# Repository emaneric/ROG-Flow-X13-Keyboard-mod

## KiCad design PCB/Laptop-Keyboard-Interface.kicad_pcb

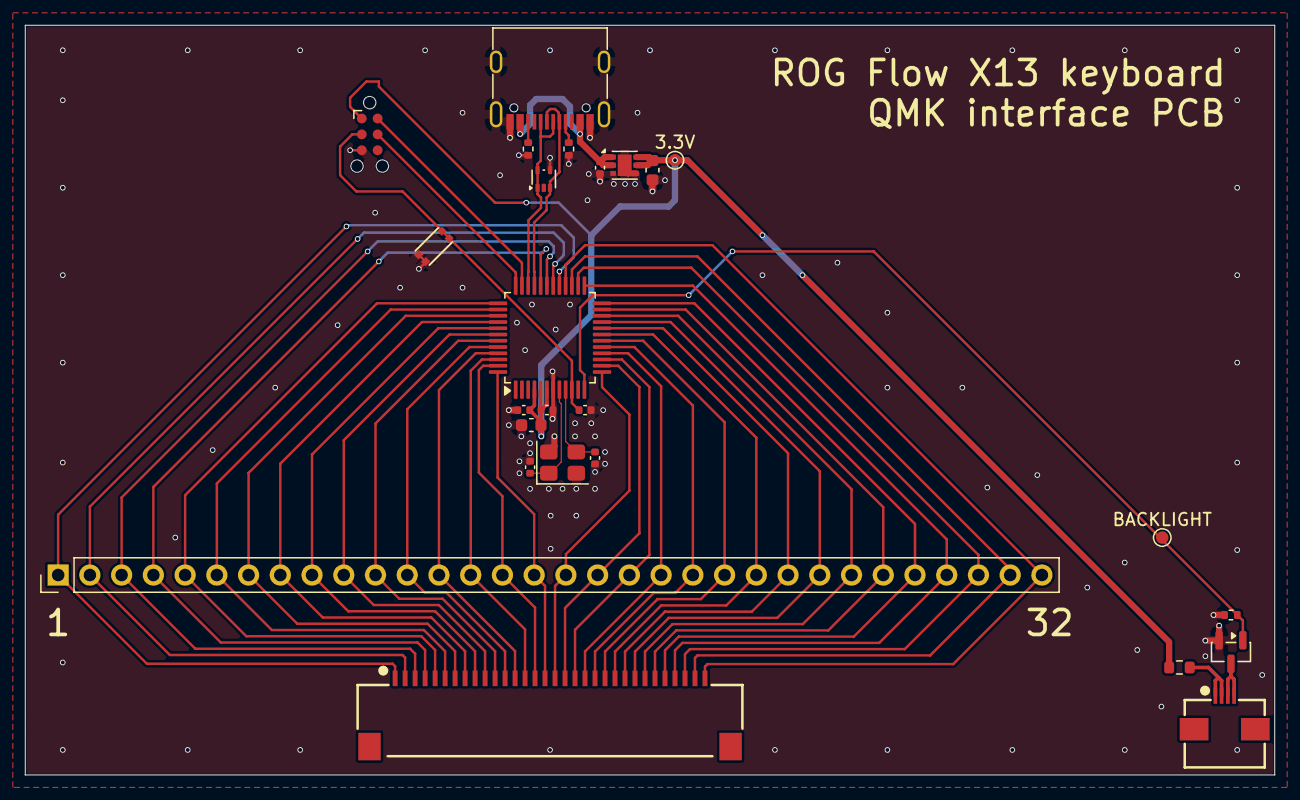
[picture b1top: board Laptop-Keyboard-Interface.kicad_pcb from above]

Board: 2 copper layers, 100.0 x 60.0 mm, 25 parts (0 on the bottom side), 47 nets.

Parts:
3.3V: TestPoint; TestPoint_Pad_D1.0mm
BACKLIGHT: TestPoint; TestPoint_Pad_D1.0mm
C1: 1uF; C_0402_1005Metric
C2, C3: 10uF; C_0603_1608Metric
C4, C5, C8: 100nF; C_0402_1005Metric
C6, C7: 15pF; C_0402_1005Metric
J1: Conn_ARM_SWD_TagConnect_TC2030-NL; Tag-Connect_TC2030-IDC-NL_2x03_P1.27mm_Vertical
J2: USB_C_Receptacle_USB2.0_16P; USB_C_Receptacle_G-Switch_GT-USB-7010ASV
J3: Conn_01x32; THD0820-32CL-SN
J4: Conn_01x32; PinHeader_1x32_P2.54mm_Vertical
J5: Conn_01x04; AFC01-S04FCC-00
Q1: AO3400A; SOT-23
R1, R2: 5.1k; R_0402_1005Metric
R3: R; R_0603_1608Metric
R4: 100k; R_0402_1005Metric
SW1: SW_SPST_4_PIN; 1TS026A-2300-0553-CT
U1: NCP187; OnSemi_WDFN6_2x2_0.65P_CASE_511BR
U2: TPD2E2U06DRL; SOT-553
U3: STM32G0B1CBTx; LQFP-48_7x7mm_P0.5mm
Y1: Crystal_GND24; Crystal_SMD_3225-4Pin_3.2x2.5mm

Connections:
+3V3: 3.3V.1, C2.2, C3.2, C4.2, C5.2, J1.1 (VCC), R3.1, U1.5 (SNS), U1.6 (VOUT), U3.4 (VBAT), U3.5 (VREF+), U3.6 (VDD)
+5V: C1.2, J2.A4 (VBUS), J2.A9 (VBUS), J2.B4 (VBUS), J2.B9 (VBUS), U1.1 (VIN), U1.2 (EN)
/1: J3.1, J4.1, U3.29 (PA9/UCPD1_DBCC1)
/2: J3.2, J4.2, U3.30 (PC6)
/3: J3.3, J4.3, U3.31 (PC7)
/4: J3.4, J4.4, U3.32 (PA10/UCPD1_DBCC2)
/5: J3.5, J4.5, U3.37 (PA15)
/6: J3.6, J4.6, U3.38 (PD0)
/7: J3.7, J4.7, U3.39 (PD1)
/8: J3.8, J4.8, U3.40 (PD2)
/9: J3.9, J4.9, U3.41 (PD3)
/10: J3.10, J4.10, U3.42 (PB3)
/11: J3.11, J4.11, U3.43 (PB4)
/12: J3.12, J4.12, U3.44 (PB5)
/13: J3.13, J4.13, U3.45 (PB6)
/14: J3.14, J4.14, U3.46 (PB7)
/15: J3.15, J4.15, U3.47 (PB8)
/16: J3.16, J4.16, U3.48 (PB9)
/17: J3.17, J4.17, U3.13 (PA2)
/18: J3.18, J4.18, U3.14 (PA3)
/19: J3.19, J4.19, U3.15 (PA4)
/20: J3.20, J4.20, U3.16 (PA5)
/21: J3.21, J4.21, U3.17 (PA6)
/22: J3.22, J4.22, U3.18 (PA7)
/23: J3.23, J4.23, U3.19 (PB0)
/24: J3.24, J4.24, U3.20 (PB1)
/25: J3.25, J4.25, U3.21 (PB2)
/26: J3.26, J4.26, U3.22 (PB10)
/27: J3.27, J4.27, U3.23 (PB11)
/28: J3.28, J4.28, U3.24 (PB12)
/29: J3.29, J4.29, U3.25 (PB13)
/30: J3.30, J4.30, U3.26 (PB14)
/31: J3.31, J4.31, U3.27 (PB15)
/32: J3.32, J4.32, U3.28 (PA8)
/BACKLIGHT: BACKLIGHT.1, Q1.1 (G), R4.1, U3.12 (PA1)
/D+: J2.A6 (D+), J2.B6 (D+), U2.1 (NC), U2.5, U3.34 (PA10/PA12)
/D-: J2.A7 (D-), J2.B7 (D-), U2.3, U3.33 (PA9/PA11)
/NRST: C8.2, J1.3 (~RESET), SW1.1 (A), SW1.2 (A), U3.10 (PF2)
/SWCLK: J1.4 (SWCLK), U3.36 (PA14)
/SWDIO: J1.2 (SWDIO), U3.35 (PA13)
GND: C1.1, C2.1, C3.1, C4.1, C5.1, C6.1, C7.1, C8.1, J1.5 (GND), J2.A1 (GND), J2.A12 (GND), J2.B1 (GND), J2.B12 (GND), J2.S1 (SHIELD), Q1.2 (S), R1.2, R2.2, R4.2, SW1.3 (B), SW1.4 (B), U1.3 (GND), U1.4 (PG), U1.7 (EP), U2.4, U3.7 (VSS), Y1.2 (G), Y1.4 (G)
unnamed: J2.A5 (CC1), R1.1
unnamed: J2.B5 (CC2), R2.1
unnamed: J5.1, J5.2, R3.2
unnamed: J5.3, J5.4, Q1.3 (D)
unnamed: C6.2, U3.8 (PF0), Y1.1
unnamed: C7.2, U3.9 (PF1), Y1.3

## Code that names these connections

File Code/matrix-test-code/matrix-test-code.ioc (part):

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Mcu.Name=STM32G0B1C(B-C-E)Tx
Mcu.Package=LQFP48
Mcu.UserName=STM32G0B1CBTx
PA1.Signal=S_TIM2_CH2
PA10.GPIOParameters=GPIO_PuPd,GPIO_Mode
PA10.GPIO_Mode=GPIO_MODE_INPUT
PA10.GPIO_PuPd=GPIO_PULLUP
PA10.Signal=GPIO_Input
PA11\ [PA9].Mode=Device
PA11\ [PA9].Signal=USB_DM
PA12\ [PA10].Mode=Device
PA12\ [PA10].Signal=USB_DP
PA13.Mode=Serial_Wire
PA13.Signal=SYS_SWDIO
PA14-BOOT0.Mode=Serial_Wire
PA14-BOOT0.Signal=SYS_SWCLK
PA15.GPIOParameters=GPIO_PuPd,GPIO_Mode
PA15.GPIO_Mode=GPIO_MODE_INPUT
PA15.GPIO_PuPd=GPIO_PULLUP
PA15.Signal=GPIO_Input
PA2.GPIOParameters=GPIO_PuPd,GPIO_Mode
PA2.GPIO_Mode=GPIO_MODE_INPUT
PA2.GPIO_PuPd=GPIO_PULLUP
PA2.Signal=GPIO_Input
PA3.GPIOParameters=GPIO_PuPd,GPIO_Mode
PA3.GPIO_Mode=GPIO_MODE_INPUT
PA3.GPIO_PuPd=GPIO_PULLUP
PA3.Signal=GPIO_Input
PA4.GPIOParameters=GPIO_PuPd,GPIO_Mode
PA4.GPIO_Mode=GPIO_MODE_INPUT
PA4.GPIO_PuPd=GPIO_PULLUP
PA4.Signal=GPIO_Input
PA5.GPIOParameters=GPIO_PuPd,GPIO_Mode
PA5.GPIO_Mode=GPIO_MODE_INPUT
PA5.GPIO_PuPd=GPIO_PULLUP
PA5.Signal=GPIO_Input
PA6.GPIOParameters=GPIO_PuPd,GPIO_Mode
PA6.GPIO_Mode=GPIO_MODE_INPUT
PA6.GPIO_PuPd=GPIO_PULLUP
PA6.Signal=GPIO_Input
PA7.GPIOParameters=GPIO_PuPd,GPIO_Mode
PA7.GPIO_Mode=GPIO_MODE_INPUT
PA7.GPIO_PuPd=GPIO_PULLUP
PA7.Signal=GPIO_Input
PA8.GPIOParameters=GPIO_PuPd,GPIO_Mode
PA8.GPIO_Mode=GPIO_MODE_INPUT
PA8.GPIO_PuPd=GPIO_PULLUP
PA8.Signal=GPIO_Input
PB0.GPIOParameters=GPIO_PuPd,GPIO_Mode
PB0.GPIO_Mode=GPIO_MODE_INPUT
PB0.GPIO_PuPd=GPIO_PULLUP
PB0.Signal=GPIO_Input
PB1.GPIOParameters=GPIO_PuPd,GPIO_Mode
PB1.GPIO_Mode=GPIO_MODE_INPUT
PB1.GPIO_PuPd=GPIO_PULLUP
PB1.Signal=GPIO_Input
PB10.GPIOParameters=GPIO_PuPd,GPIO_Mode
PB10.GPIO_Mode=GPIO_MODE_INPUT
PB10.GPIO_PuPd=GPIO_PULLUP
PB10.Signal=GPIO_Input
PB11.GPIOParameters=GPIO_PuPd,GPIO_Mode
PB11.GPIO_Mode=GPIO_MODE_INPUT
PB11.GPIO_PuPd=GPIO_PULLUP
PB11.Signal=GPIO_Input
PB12.GPIOParameters=GPIO_PuPd,GPIO_Mode
PB12.GPIO_Mode=GPIO_MODE_INPUT
PB12.GPIO_PuPd=GPIO_PULLUP
PB12.Signal=GPIO_Input
PB13.GPIOParameters=GPIO_PuPd,GPIO_Mode
PB13.GPIO_Mode=GPIO_MODE_INPUT
PB13.GPIO_PuPd=GPIO_PULLUP
PB13.Signal=GPIO_Input
PB14.GPIOParameters=GPIO_PuPd,GPIO_Mode
PB14.GPIO_Mode=GPIO_MODE_INPUT
PB14.GPIO_PuPd=GPIO_PULLUP
PB14.Signal=GPIO_Input
PB15.GPIOParameters=GPIO_PuPd,GPIO_Mode
PB15.GPIO_Mode=GPIO_MODE_INPUT
PB15.GPIO_PuPd=GPIO_PULLUP
PB15.Signal=GPIO_Input
PB2.GPIOParameters=GPIO_PuPd,GPIO_Mode
PB2.GPIO_Mode=GPIO_MODE_INPUT
PB2.GPIO_PuPd=GPIO_PULLUP
PB2.Signal=GPIO_Input
PB3.GPIOParameters=GPIO_PuPd,GPIO_Mode
PB3.GPIO_Mode=GPIO_MODE_INPUT
PB3.GPIO_PuPd=GPIO_PULLUP
PB3.Signal=GPIO_Input
PB4.GPIOParameters=GPIO_PuPd,GPIO_Mode
PB4.GPIO_Mode=GPIO_MODE_INPUT
PB4.GPIO_PuPd=GPIO_PULLUP
PB4.Signal=GPIO_Input
PB5.GPIOParameters=GPIO_PuPd,GPIO_Mode
PB5.GPIO_Mode=GPIO_MODE_INPUT
PB5.GPIO_PuPd=GPIO_PULLUP
PB5.Signal=GPIO_Input
PB6.GPIOParameters=GPIO_PuPd,GPIO_Mode
PB6.GPIO_Mode=GPIO_MODE_INPUT
PB6.GPIO_PuPd=GPIO_PULLUP
PB6.Signal=GPIO_Input
PB7.GPIOParameters=GPIO_PuPd,GPIO_Mode
PB7.GPIO_Mode=GPIO_MODE_INPUT
PB7.GPIO_PuPd=GPIO_PULLUP
PB7.Signal=GPIO_Input
PB8.GPIOParameters=GPIO_PuPd,GPIO_Mode
PB8.GPIO_Mode=GPIO_MODE_INPUT
PB8.GPIO_PuPd=GPIO_PULLUP
PB8.Signal=GPIO_Input
PB9.GPIOParameters=GPIO_PuPd,GPIO_Mode
PB9.GPIO_Mode=GPIO_MODE_INPUT
PB9.GPIO_PuPd=GPIO_PULLUP
PB9.Signal=GPIO_Input
PC7.GPIOParameters=GPIO_PuPd
PC7.GPIO_PuPd=GPIO_PULLDOWN
PC7.Signal=GPIO_Output
PD0.GPIOParameters=GPIO_PuPd,GPIO_Mode
PD0.GPIO_Mode=GPIO_MODE_INPUT
PD0.GPIO_PuPd=GPIO_PULLUP
PD0.Signal=GPIO_Input
PD1.GPIOParameters=GPIO_PuPd,GPIO_Mode
PD1.GPIO_Mode=GPIO_MODE_INPUT
PD1.GPIO_PuPd=GPIO_PULLUP
PD1.Signal=GPIO_Input
PD2.GPIOParameters=GPIO_PuPd,GPIO_Mode
PD2.GPIO_Mode=GPIO_MODE_INPUT
PD2.GPIO_PuPd=GPIO_PULLUP
PD2.Signal=GPIO_Input
PD3.GPIOParameters=GPIO_PuPd,GPIO_Mode
PD3.GPIO_Mode=GPIO_MODE_INPUT
PD3.GPIO_PuPd=GPIO_PULLUP
PD3.Signal=GPIO_Input
RCC.HSE_VALUE=8000000
RCC.SYSCLKFreq_VALUE=16000000
board=custom

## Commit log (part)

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2026-05-14 -updated qmk config
2026-05-14 Added caps lock control
2026-05-14 -Added volume media key controls
2026-05-14 -regenrated cube mx, made pa1 an output
2026-05-14 -Added PWM backlight control
2026-05-14 -Added jump to bootloader by holding ROG button
